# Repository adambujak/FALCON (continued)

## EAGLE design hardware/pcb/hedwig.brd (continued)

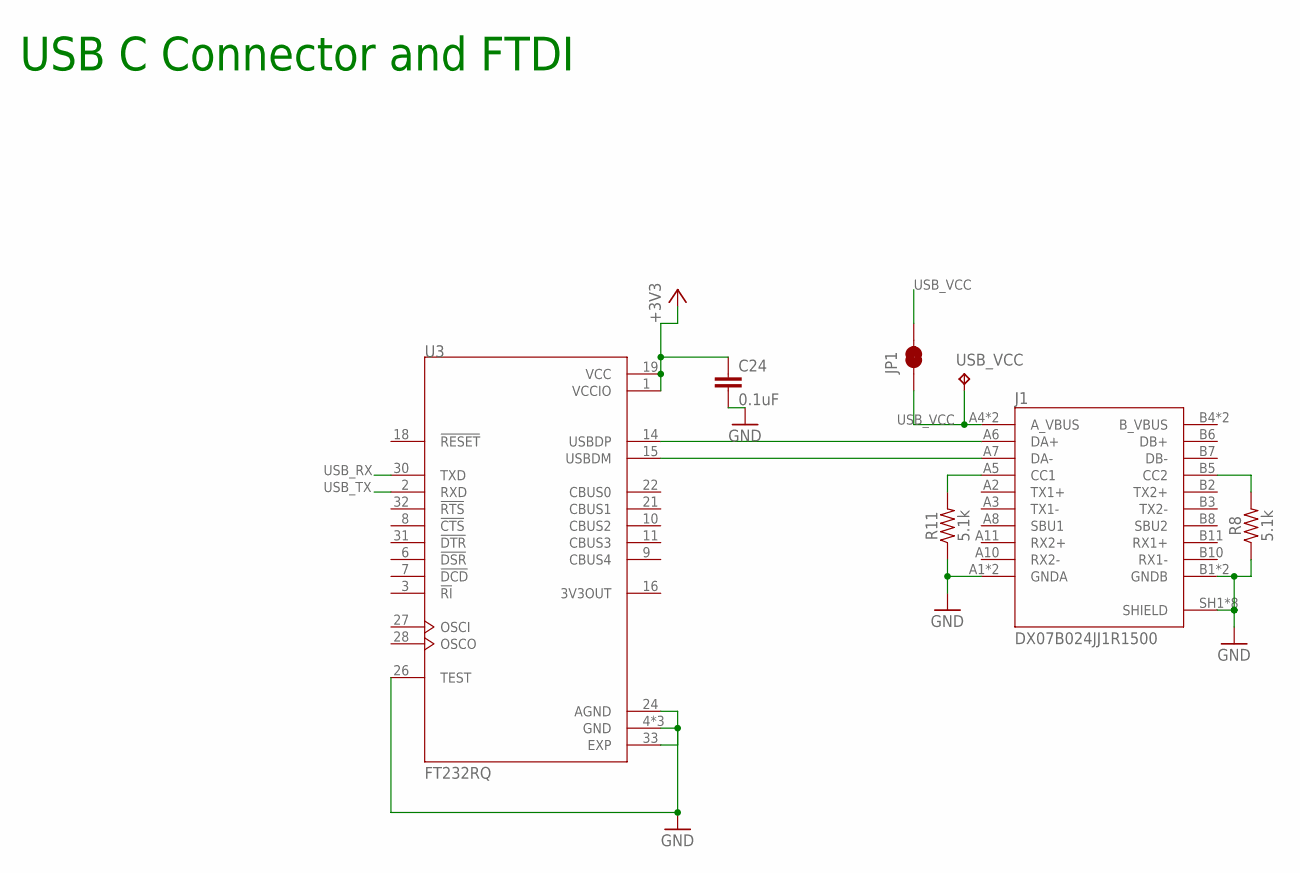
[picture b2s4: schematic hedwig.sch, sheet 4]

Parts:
C24: 0.1uF; 0603@1
J1: DX07B024JJ1R1500; JAE_DX07B024JJ1R1500
JP1: JUMPER-SMT_2_NC_TRACE_SILK; SMT-JUMPER_2_NC_TRACE_SILK
R8, R11: 5.1k; 0603
U3: FT232RQ; QFN50P500X500X90-33N
USB_VCC: TPB2,54; B2,54

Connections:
+3V3: C24.1, U3.1 (VCCIO), U3.19 (VCC); also elsewhere on the board
B_VBUS: J1.B4 (B_VBUS), J1.B9 (B_VBUS)
GND: C24.2, J1.A1 (GNDA), J1.A12 (GNDA), J1.B1 (GNDB), J1.B12 (GNDB), J1.SH1 (SHIELD), J1.SH2 (SHIELD), J1.SH3 (SHIELD), J1.SH4 (SHIELD), J1.SH5 (SHIELD), J1.SH6 (SHIELD), J1.SH7 (SHIELD), J1.SH8 (SHIELD), R8.1, R11.1, U3.4 (GND), U3.17 (GND), U3.20 (GND), U3.24 (AGND), U3.26 (TEST), U3.33 (EXP); also elsewhere on the board
unnamed: J1.B5 (CC2), R8.2
unnamed: J1.A6 (DA+), U3.14 (USBDP)
unnamed: J1.A7 (DA-), U3.15 (USBDM)
unnamed: J1.A5 (CC1), R11.2
USB_RX: U3.30 (TXD); also elsewhere on the board
USB_TX: U3.2 (RXD); also elsewhere on the board
USB_VCC: J1.A4 (A_VBUS), J1.A9 (A_VBUS), JP1.1, JP1.2, USB_VCC.TP; also elsewhere on the board

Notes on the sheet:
USB C Connector and FTDI

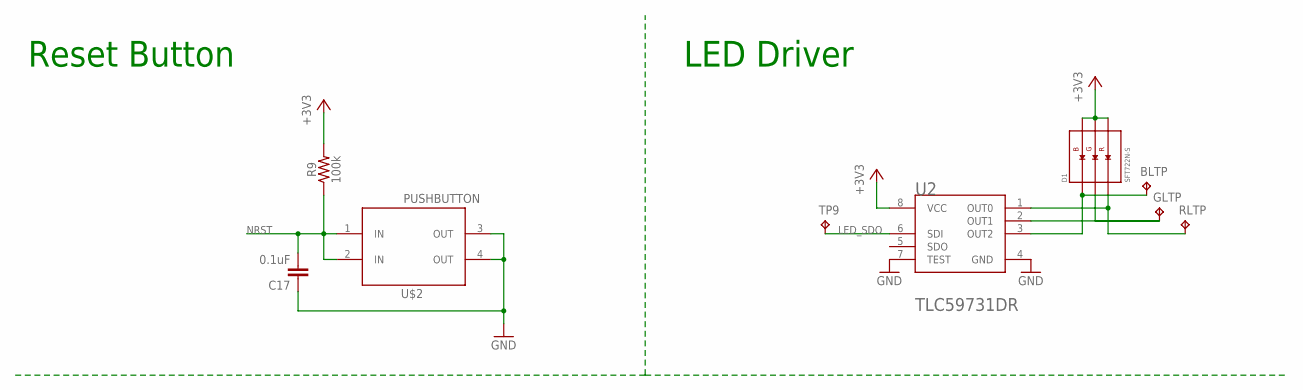
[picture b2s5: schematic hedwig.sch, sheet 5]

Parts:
BLTP: TPB1,27; B1,27
C17: 0.1uF; 0603
D1: SFT722N-S; LED_SFT722N-S
GLTP: TPB1,27; B1,27
R9: 100k; 0603
RLTP: TPB1,27; B1,27
TP9: TPB1,27; B1,27
U2: TEXAS_INSTRUMENTS_TLC59731DRTEXAS_INSTRUMENTS_TLC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; TEXAS_INSTRUMENTS_TLC59731DR_0
U$2: PUSHBUTTON; PUSH_BUTTON

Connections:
+3V3: D1.4 (RA), D1.5 (GA), D1.6 (BA), R9.2, U2.8 (VCC); also elsewhere on the board
GND: C17.1, U2.4 (GND), U2.7 (TEST), U$2.3 (OUT), U$2.4 (OUT); also elsewhere on the board
LED_SDO: TP9.TP, U2.6 (SDI); also elsewhere on the board
unnamed: BLTP.TP, D1.1 (BC), U2.3 (OUT2)
unnamed: D1.3 (RC), RLTP.TP, U2.1 (OUT0)
unnamed: D1.2 (GC), GLTP.TP, U2.2 (OUT1)
NRST: C17.2, R9.1, U$2.1 (IN), U$2.2 (IN); also elsewhere on the board

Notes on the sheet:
Reset Button
LED Driver

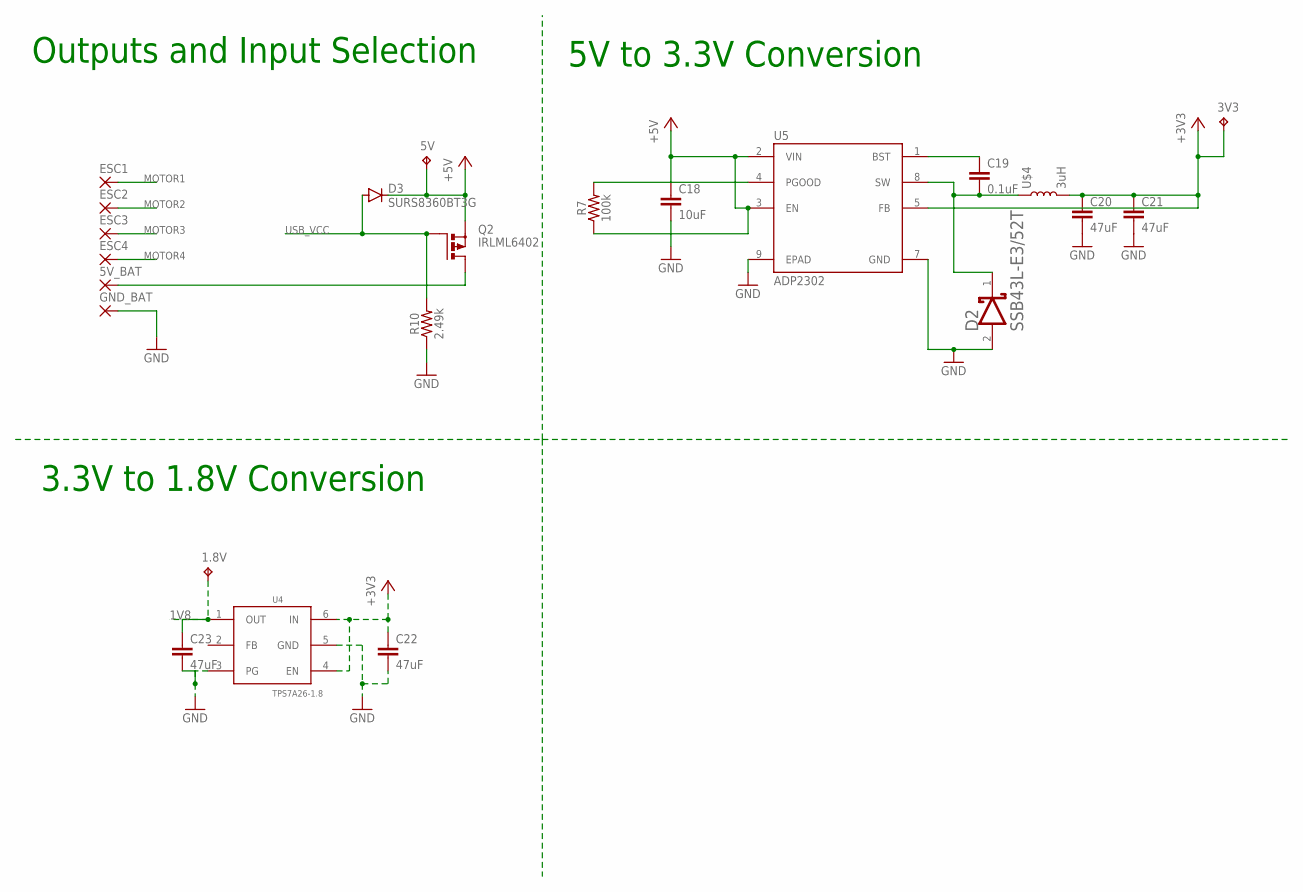
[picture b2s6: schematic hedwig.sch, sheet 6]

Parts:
1.8V, 3V3, 5V: TPB2,54; B2,54
5V_BAT: 2,54/1,0
C18: 10uF; 0603@1
C19: 0.1uF; 0603@1
C20, C21, C22, C23: 47uF; 0603@1
D2: SSB43L; VISHAY_SSB43L-E3-52T_0
D3: SURS8360BT3G; SMB
ESC1, ESC2, ESC3, ESC4: SMD2; SMD1,27-2,54
GND_BAT: 2,54/1,0
Q2: IRLML6402; SOT-23
R7: 100k; 0603
R10: 2.49k; 0603
U4: TPS7A26-1.8; WSON
U5: ADP2302; SOIC127P600X175-9N
U$4: 3uH; REG_INDUCTOR

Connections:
1V8: 1.8V.TP, C23.1, U4.1 (OUT); also elsewhere on the board
+3V3: 3V3.TP, C20.1, C21.1, C22.1, U4.4 (EN), U4.6 (IN), U5.5 (FB), U$4.@2 (2); also elsewhere on the board
+5V: 5V.TP, C18.1, D3.@2 (C), Q2.P2 (S), R7.1, U5.2 (VIN), U5.3 (EN)
GND: C18.2, C20.2, C21.2, C22.2, C23.2, D2.2 (ANODE), GND_BAT.1, R10.1, U4.3 (PG), U4.5 (GND), U5.7 (GND), U5.9 (EPAD); also elsewhere on the board
MOTOR1: ESC1.1; also elsewhere on the board
MOTOR2: ESC2.1; also elsewhere on the board
MOTOR3: ESC3.1; also elsewhere on the board
MOTOR4: ESC4.1; also elsewhere on the board
unnamed: C19.1, U5.1 (BST)
unnamed: R7.2, U5.4 (PGOOD)
unnamed: C19.2, D2.1 (CATHODE), U5.8 (SW), U$4.@1 (1)
unnamed: 5V_BAT.1, Q2.P3 (D)
USB_VCC: D3.@1 (A), Q2.P1 (G), R10.2; also elsewhere on the board

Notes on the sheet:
Outputs and Input Selection
5V to 3.3V Conversion
3.3V to 1.8V Conversion

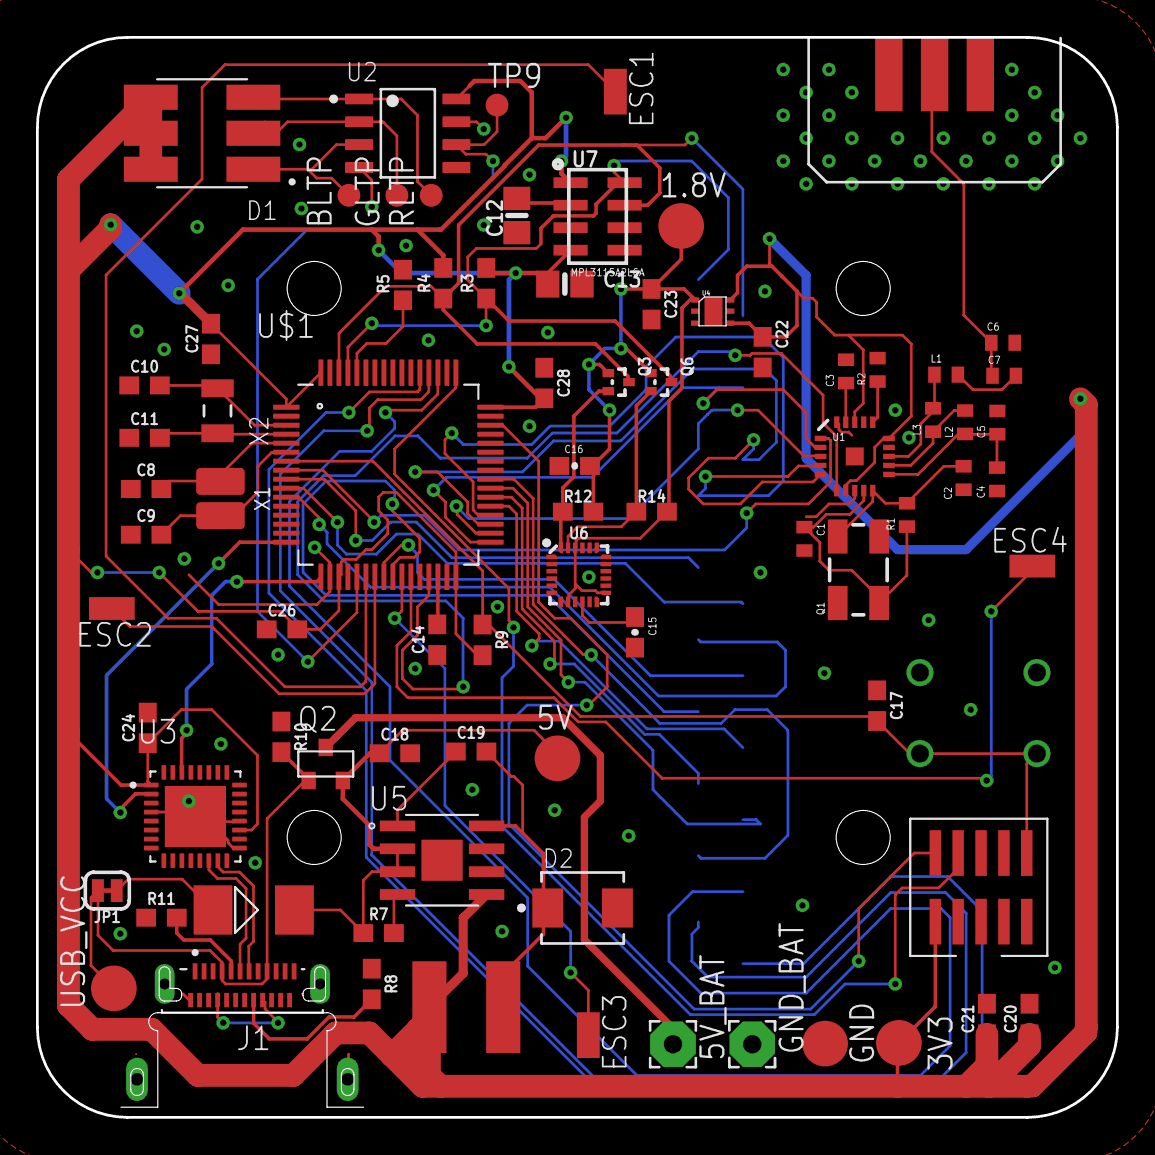
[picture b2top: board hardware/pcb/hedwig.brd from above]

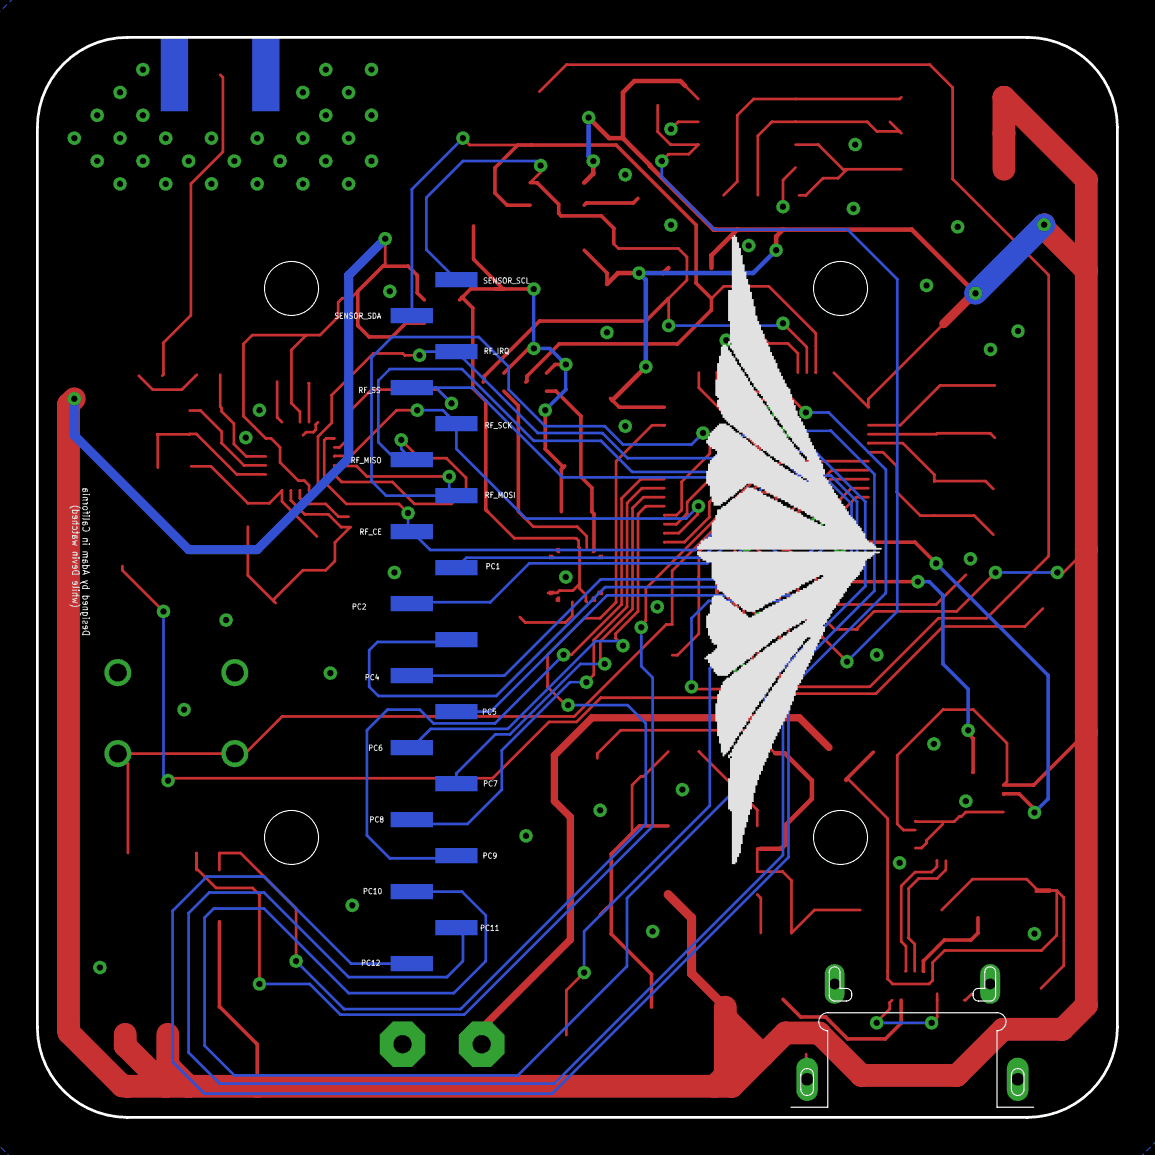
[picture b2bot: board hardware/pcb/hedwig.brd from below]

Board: 2 copper layers, 60.0 x 60.0 mm, 85 parts (5 on the bottom side), 66 nets.

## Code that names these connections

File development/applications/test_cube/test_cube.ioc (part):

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PB13.GPIOParameters=GPIO_Label
Mcu.UserName=STM32F412ZGTx
PD9.GPIOParameters=GPIO_Label
PA14.GPIO_Label=TCK
RCC.SYSCLKSourceVirtual=RCC_SYSCLKSOURCE_PLLCLK
PC6.GPIO_Label=RF_CE
PA3.GPIOParameters=GPIO_ModeDefaultPP
PB13.GPIO_Label=RF_SCK
PB13.Signal=SPI2_SCK
PB15.Signal=SPI2_MOSI
PD9.Mode=Asynchronous
RCC.SYSCLKSource=RCC_SYSCLKSOURCE_PLLCLK
PA3.GPIO_ModeDefaultPP=GPIO_MODE_AF_OD
PH0\ -\ OSC_IN.Signal=RCC_OSC_IN
PD8.GPIOParameters=GPIO_Label
PD8.Signal=USART3_TX
RCC.HSE_VALUE=8000000
PB12.GPIO_Label=RF_SS
PC14-OSC32_IN.Mode=LSE-External-Oscillator
PA14.Mode=Serial_Wire
PB14.Mode=Full_Duplex_Master
PB3.GPIOParameters=GPIO_Label
PH0\ -\ OSC_IN.GPIOParameters=GPIO_Label
PA13.GPIOParameters=GPIO_Label
Mcu.Package=LQFP144
PC6.GPIO_PuPd=GPIO_PULLUP
PB13.Mode=Full_Duplex_Master
PC6.GPIO_Speed=GPIO_SPEED_FREQ_HIGH
PA3.Signal=USART2_RX
PB3.GPIO_Label=SWO
PC15-OSC32_OUT.Mode=LSE-External-Oscillator
PD9.GPIO_Label=STLK_TX [STM32F103CBT6_PA2]
PH1\ -\ OSC_OUT.Mode=HSE-External-Clock-Source
PC6.Signal=GPIO_Output
PD9.Signal=USART3_RX
PC14-OSC32_IN.Signal=RCC_OSC32_IN
boardIOC=true
PD8.GPIO_Label=STLK_RX [STM32F103CBT6_PA3]
PA3.Mode=Asynchronous
PA13.Signal=SYS_JTMS-SWDIO
PH0\ -\ OSC_IN.Mode=HSE-External-Clock-Source
PC15-OSC32_OUT.Signal=RCC_OSC32_OUT
PD8.Mode=Asynchronous
PB10.Signal=GPXTI10
PB14.Signal=SPI2_MISO
PH1\ -\ OSC_OUT.Signal=RCC_OSC_OUT
board=NUCLEO-F412ZG
PB15.Mode=Full_Duplex_Master
PA13.Mode=Serial_Wire
Mcu.Name=STM32F412Z(E-G)Tx
PA2.Signal=USART2_TX
PA13.GPIO_Label=TMS
PB3.Signal=SYS_JTDO-SWO
RCC.SYSCLKFreq_VALUE=96000000
PA14.GPIOParameters=GPIO_Label
PA14.Signal=SYS_JTCK-SWCLK
PC6.GPIOParameters=GPIO_Speed,GPIO_PuPd,GPIO_Label
PA2.Mode=Asynchronous
PH0\ -\ OSC_IN.GPIO_Label=MCO
PB12.GPIOParameters=GPIO_Label
PB12.Signal=SPI2_NSS

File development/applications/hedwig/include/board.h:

#ifndef BOARD_H
#define BOARD_H

#include "stm32f4xx_hal.h"
#include "stm32f4xx_ll_bus.h"
#include "stm32f4xx_ll_gpio.h"
#include "stm32f4xx_ll_pwr.h"
#include "stm32f4xx_ll_rcc.h"
#include "stm32f4xx_ll_system.h"
#include "stm32f4xx_ll_tim.h"
#include "stm32f4xx_ll_usart.h"
#include "stm32f4xx_ll_utils.h"

#define SYSCLK_FREQ             96000000

/* System Time */
#define SYSTEM_TIME_TIMER       TIM2
#define SYSTEM_TIME_CLK_EN()    LL_APB1_GRP1_EnableClock(LL_APB1_GRP1_PERIPH_TIM2)

/* LEDS */
#ifdef BOARD_V1
#define FLN_LED_CLK_ENABLE()                     __HAL_RCC_GPIOA_CLK_ENABLE();
#define FLN_LED_PIN                              GPIO_PIN_5
#define FLN_LED_PORT                             GPIOA
#endif

#define FLN_LED_AF                               GPIO_AF2_TIM2
#define FLN_LED_TIMER                            TIM2
#define FLN_LED_TIMER_IRQ                        TIM2_IRQn
#define FLN_LED_TIMER_IRQ_Handler                TIM2_IRQHandler
#define FLN_LED_TIMER_CLK_ENABLE()               __HAL_RCC_TIM2_CLK_ENABLE()

/* UART */
#define UART                                     USART2
#define UART_CLK_EN()                            LL_APB1_GRP1_EnableClock(LL_APB1_GRP1_PERIPH_USART2)
#define GPIO_UART_CLK_EN()                       LL_AHB1_GRP1_EnableClock(LL_AHB1_GRP1_PERIPH_GPIOA)

#define UART_FORCE_RESET()                       __HAL_RCC_USART2_FORCE_RESET()
#define UART_RELEASE_RESET()                     __HAL_RCC_USART2_RELEASE_RESET()

#define UART_GPIO_PORT                           GPIOA
#define UART_GPIO_AF                             GPIO_AF7_USART2
#define UART_TX_PIN                              GPIO_PIN_2
#define UART_RX_PIN                              GPIO_PIN_3

#define UART_BAUDRATE                            1000000

#define UART_IRQn                                USART2_IRQn
#define UART_IRQHandler                          USART2_IRQHandler

/* Sensors */
#define FLN_SENSORS_I2C                          I2C1
#define FLN_SENSORS_I2C_CLK_ENABLE()             __HAL_RCC_I2C1_CLK_ENABLE()
#define FLN_SENSORS_I2C_SDA_GPIO_CLK_ENABLE()    __HAL_RCC_GPIOB_CLK_ENABLE()
#define FLN_SENSORS_I2C_SCL_GPIO_CLK_ENABLE()    __HAL_RCC_GPIOB_CLK_ENABLE()

#define FLN_SENSORS_I2C_FORCE_RESET()            __HAL_RCC_I2C1_FORCE_RESET()
#define FLN_SENSORS_I2C_RELEASE_RESET()          __HAL_RCC_I2C1_RELEASE_RESET()

#define FLN_SENSORS_I2C_SCL_PIN                  GPIO_PIN_8
#define FLN_SENSORS_I2C_SCL_GPIO_PORT            GPIOB
#define FLN_SENSORS_I2C_SDA_PIN                  GPIO_PIN_9
#define FLN_SENSORS_I2C_SDA_GPIO_PORT            GPIOB
#define FLN_SENSORS_I2C_SCL_SDA_AF               GPIO_AF4_I2C1

#define FLN_SENSORS_I2C_SPEEDCLOCK               400000
#define FLN_SENSORS_I2C_DUTYCYCLE                I2C_DUTYCYCLE_2

/* IMU */
#define IMU_IRQ_GPIO_CLK_ENABLE()                __HAL_RCC_GPIOA_CLK_ENABLE()
#define IMU_IRQ_PIN                              GPIO_PIN_8
#define IMU_IRQ_GPIO_PORT                        GPIOA

/* MOTORS */
#define FLN_MOTOR_TIMER                          TIM3
#define FLN_MOTOR_TIMER_CLK_ENABLE()             __HAL_RCC_TIM3_CLK_ENABLE()
#define FLN_MOTOR_GPIO_CLK_ENABLE()              __HAL_RCC_GPIOA_CLK_ENABLE(); \
  __HAL_RCC_GPIOB_CLK_ENABLE();

#define FLN_MOTOR_GPIO_PORT_CHANNEL1             GPIOA
#define FLN_MOTOR_GPIO_PORT_CHANNEL2             GPIOA
#define FLN_MOTOR_GPIO_PORT_CHANNEL3             GPIOB
#define FLN_MOTOR_GPIO_PORT_CHANNEL4             GPIOB
#define FLN_MOTOR_GPIO_PIN_CHANNEL1              GPIO_PIN_6
#define FLN_MOTOR_GPIO_PIN_CHANNEL2              GPIO_PIN_7
#define FLN_MOTOR_GPIO_PIN_CHANNEL3              GPIO_PIN_0
#define FLN_MOTOR_GPIO_PIN_CHANNEL4              GPIO_PIN_1
#define FLN_MOTOR_GPIO_AF_CHANNEL1               GPIO_AF2_TIM3
#define FLN_MOTOR_GPIO_AF_CHANNEL2               GPIO_AF2_TIM3
#define FLN_MOTOR_GPIO_AF_CHANNEL3               GPIO_AF2_TIM3
#define FLN_MOTOR_GPIO_AF_CHANNEL4               GPIO_AF2_TIM3

/* RF */
#define RF_SPI                                   SPI2
#define RF_SPI_CLK_ENABLE()                      __HAL_RCC_SPI2_CLK_ENABLE()
#define RF_SPI_SCK_GPIO_CLK_ENABLE()             __HAL_RCC_GPIOB_CLK_ENABLE()
#define RF_SPI_MISO_GPIO_CLK_ENABLE()            __HAL_RCC_GPIOB_CLK_ENABLE()
#define RF_SPI_MOSI_GPIO_CLK_ENABLE()            __HAL_RCC_GPIOB_CLK_ENABLE()
#define RF_GPIO_CLK_ENABLE()                     __HAL_RCC_GPIOB_CLK_ENABLE(); \
  __HAL_RCC_GPIOC_CLK_ENABLE()
#define RF_IRQ_GPIO_CLK_ENABLE()                 __HAL_RCC_GPIOB_CLK_ENABLE()

#define RF_SPI_FORCE_RESET()                     __HAL_RCC_SPI2_FORCE_RESET()
#define RF_SPI_RELEASE_RESET()                   __HAL_RCC_SPI2_RELEASE_RESET()

#define RF_IRQ_PIN                               GPIO_PIN_10
#define RF_IRQ_GPIO_PORT                         GPIOB
#define RF_CE_PIN                                GPIO_PIN_6
#define RF_CE_GPIO_PORT                          GPIOC
#define RF_SPI_SS_PIN                            GPIO_PIN_12
#define RF_SPI_SS_GPIO_PORT                      GPIOB
#define RF_SPI_SCK_PIN                           GPIO_PIN_13
#define RF_SPI_SCK_GPIO_PORT                     GPIOB
#define RF_SPI_SCK_AF                            GPIO_AF5_SPI2
#define RF_SPI_MISO_PIN                          GPIO_PIN_14
#define RF_SPI_MISO_GPIO_PORT                    GPIOB
#define RF_SPI_MISO_AF                           GPIO_AF5_SPI2
#define RF_SPI_MOSI_PIN                          GPIO_PIN_15
#define RF_SPI_MOSI_GPIO_PORT                    GPIOB
#define RF_SPI_MOSI_AF                           GPIO_AF5_SPI2

#endif  // BOARD_H

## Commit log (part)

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2020-10-05 Format code
2020-10-05 Move bringup code to bsp
2020-10-06 Add tags to gitignore
2020-10-06 gitignore update and cleanup (#12)
    * Remove unused function prototype
    * Add tags to gitignore
2020-10-15 i2c working
2020-10-16 added mpu sdk
2020-10-16 Simplify logger and implement macro
2020-10-16 review changes
2020-10-17 changed to HAL_mem_read/write, works on both sensors now
2020-10-17 add std gnu flag (#17)
2020-10-17 Rename i2c module definitions
2020-10-17 Add -Werror flag to makefile
2020-10-17 Add sensors i2c
2020-10-17 Fix function declarations to match functions defs
2020-10-17 Change pins
2020-10-21 Add motor control with PWM (#18)
    * Add motor control with PWM
    * Change pins
    * Fix assert
2020-10-21 Add custom spi functions to HAL
2020-10-25 Add pcb and schematic
2020-10-26 updated schematic and pcb
2020-10-27 add flash python script and add to makefile
2020-10-28 Pcb overhall - put imu in middle, made board square
2020-10-28 Add logo to that pcb
2020-10-28 Added pics, pdf, fixed silkscreen, and added more vias
2020-10-29 working with restart
2020-10-30 sending frf
2020-10-31 getting interrupt from rx
2020-10-31 fix max_rt bug
2020-10-31 Move rx clear rxPowerUp
2020-11-04 grabbed modified mpu9250 python stuff
2020-11-06 Fix major issues in hardware
2020-11-09 added ICM and fimu stuff to makefile
2020-11-10 added driver dependency files
2020-11-10 added working fimu library files
2020-11-11 add flash python script and add to makefile (#20)
2020-11-11 - Add support for new board - Fix FreeRTOS delay bug (if delayed before scheduler starts, hard fault) - Code cleanup in bsp
2020-11-11 add jlink serial id
2020-11-11 Add support for new board and some other fixes (#23)
    * - Add support for new board
    - Fix FreeRTOS delay bug (if delayed before scheduler starts, hard fault)
    - Code cleanup in bsp
    * add jlink serial id
2020-11-12 working
2020-11-12 added set color function to header
2020-11-12 Abstract timer handler
2020-11-13 rf working
2020-11-13 Fix FRF library, and add to stm (#26)
    * - Add support for new board
    - Fix FreeRTOS delay bug (if delayed before scheduler starts, hard fault)
    - Code cleanup in bsp
    * Add custom spi functions to HAL
    Add spi to v2 app and add frf
    Sending data
2020-11-13 Add support for LED driver on new board (#25)
    * LED ON
    * working
    * Blinking led
    * added set color function to header
    * Abstract timer handler
2020-11-15 removed WError for now
2020-11-15 added MPL driver
2020-11-15 general setup for sensors task
2020-11-15 updated sensors task for different rate barometer readings
2020-11-15 sensors task and barometer library setup
2020-11-15 improved fbaro calibration function
2020-11-19 added motor init function from testing on hardware
2020-12-17 changes for new board
2020-12-17 add ozone debug files
2020-12-17 schematic and pcb update
2020-12-22 Reduce motor delay time, and increase sensor task priority
2020-12-30 fix irq naming for imu
2021-01-29 add albus - stm32
    deleted eclipse
    Add frf process so it'll work
2021-01-29 fix disco board issue in makefile
2021-01-29 implement radio common into device com
2021-01-30 RF packets sending back and forth feature (#28)
    * add assert to both hedwig and albus
    * add albus - stm32
    deleted eclipse
    Add frf process so it'll work
    * add radio common to makefile
    * fix disco board issue in makefile
2021-02-01 Schematic Update - Fix USB C port reversablilty issue Board Update - Fix USB C port reversablilty issue BOM Update - Fix incorrect logic level shift FET - Fix multiple entries for same parts
2021-03-13 add grinbuf
2021-03-13 Merge grinbuf library and test infrastructure (#30)
    * add grinbuf
    * add testing framework
2021-03-13 add falcon packet lib
2021-03-13 change VDISCO to DISCO
2021-03-14 increase stack and heap size for albus
2021-03-14 Add common defines
2021-03-14 changes to frf
2021-03-14 albus device com changes
2021-03-14 Sending falcon packets back and forth (#33)
    * changes to frf
    * albus device com changes
    * hedwig changes to receive falcon packets
2021-03-14 fix makefile board define
2021-03-14 fix makefile includes
2021-03-14 rename falcon_v2 to hedwig
2021-03-14 rename falcon_v2 to hedwig (#35)
2021-03-14 fix test paths (#37)
2021-03-14 sensors task running alongside device com
2021-03-14 temp sensors.c commit
2021-03-14 renamed modes
2021-03-14 fix for imu hook file using taskDelay
2021-03-15 clean up makefile output
2021-03-15 remove eclipse files"
2021-03-15 add python packet generation
2021-04-02 add power of two assert
2021-04-02 receiving packets - todo figure out python exit
2021-04-02 was working before but not receiving uart now
2021-04-02 start adding cornelius
2021-04-02 monitor scrolling
2021-04-02 new albus has uart
2021-04-02 albus rewrite
2021-04-02 cornelius serial monitor scrolling back to top
2021-04-02 sending frames to albus
2021-04-02 fix system time hard fault
2021-04-02 cleanup main
2021-04-02 add led toggle to error handler and start device com task
2021-04-02 wrap up system time
2021-04-02 I went beast mode by accident - Implement new logger interface - Start deleting bsp from hedwig - Fix clock issue on hedwig - Fix makefile hedwig
2021-04-02 big rewrite (#40)
    * start adding cornelius
    * update python fp to return encoded bytearray
    * monitor scrolling
    * was working before but not receiving uart now
    * receiving packets - todo figure out python exit
    * idk
2021-04-03 gettign interrupts now
    revert ld
2021-04-03 revert hedwig changes'
2021-04-03 fix rf on albus (#41)
    fix rf on albus,
    add hal back
2021-04-03 change system time variable names (#42)
    move system time to common
    fix board.h
2021-04-05 remove fifo
2021-04-05 change delay from us
2021-04-05 sending ack with payload
2021-04-05 remove frf mutex
2021-04-05 move decoder into device com
2021-04-05 move sending and getting into device com
2021-04-05 add public radio functions
2021-04-05 add radio fifo
2021-04-05 decouple frf_getPacket
2021-04-05 lower device com priority
2021-04-05 Radios talking reliably back and forth with acks (#43)
    * speed up write time
    * working with dynamic
    * sending ack with payload
    * change delay from us
    * remove unnecessary irq clear
    * remove fifo
2021-04-09 fix warnings in ICM driver
2021-04-09 add ozone files to gitignore
2021-04-09 change clang-format
2021-04-09 change log levels
2021-04-09 general cleanup
2021-04-09 radio naming and logic changes
2021-04-09 change radio functions
2021-04-09 change system time timer
2021-04-10 run formatter
2021-04-10 formatter changes
2021-04-10 add artwork
2021-04-11 data from device com into flight control using mutex
2021-04-11 tried to implement task notif for flight control
2021-04-11 got software timer working with task notification
2021-04-11 added function for getting output data from flight control
2021-04-11 added simple FC mode support to RF stuff, hedwig side sending stuff added but commentented out
2021-04-11 turned on sensors and FC in main, rename in FC xTaskCreate
2021-04-11 MAJOR ERROR LOCATED
2021-04-11 fixed barometer problem, device com sensors and FC working at once
2021-04-11 cleanup
2021-04-11 update clang_format switch case indent
2021-04-11 add fifo to makefile
2021-04-11 fix falcon packet bugs
2021-04-11 remove albus test code
2021-04-11 change falcon packet decoding scheme - include header all the way through
2021-04-11 device com sending nicely
2021-04-11 add features to falcon packet
2021-04-11 fixup hedwig device com
2021-04-11 renamed rf_process and added writing back to cornelius
2021-04-11 add packet queuing to hedwig
2021-04-12 created motors emergency stop and added to all error handlers
2021-04-12 changed to motors_off call in FC
2021-04-12 add sending test response to device com
2021-04-12 disable logging on albus
2021-04-12 Finally sending data through system (#50)
    * add new packet for testing
    ''
    * add sending test response to device com
    * disable logging on albus
    * disable gui, and send test query
2021-04-12 remove *.pyc files from repo
2021-04-12 add decode functions to falcon_packet
2021-04-12 fixed fp
2021-04-12 Add decode to python fp (#51)
    * remove *.pyc files from repo
    * add decode functions to falcon_packet
    * remove test function from cornelius
    * fixed fp
2021-04-14 make flashing more betterer for hedwig
2021-04-15 current debug session
2021-04-15 change time
2021-04-15 add decoder
2021-04-15 add to dict method
2021-04-15 add radio stats packet
2021-04-15 remove vscode files
2021-04-15 fix falcon packet path
2021-04-16 Sending data back and forth from cornelius (#54)
    * current debug session
    * change time
    * revert albus changes
    * add decoder
    * add to dict method
    * add input to cornelius.py
2021-04-16 add stm32cubide folder to gitignore
2021-04-17 update clang format
2021-04-17 add falcon_packet
2021-04-17 add c ringbuf and libcrc
2021-04-17 update libraries to use submodules properly (#56)
    * remove libcrc and c-ringbuf
    * delete falcon_packet
    * add falcon_packet
    * add c ringbuf and libcrc
    * update falcon packet
2021-04-17 fixed path in unity submodule (#57)
2021-04-17 update falcon_packet lib
2021-04-18 calibration command working
2021-04-18 remove unused led code
2021-04-18 modified calib enum
2021-04-20 Change device com - Always send multiple of 32 to radio - Add status process
2021-04-20 add radio status logging
2021-04-20 adam fix this loser
2021-04-20 increase data rate on radio
2021-04-20 lower rf_tx interval on albus
2021-04-20 changes to python
2021-04-20 increase radio tx buffer size
2021-04-23 setting up for rotor stand test
2021-04-27 minor fixes to sensor libs
2021-04-28 tunable parameter testing working
2021-05-07 kind of working
2021-05-07 added PID param tuning commands, falcon was hovering somewhat stably on test stand before disaster struck
2021-05-18 made hover constant a tunable parameter
2021-05-19 seperated controller params into seperate packets
2021-05-19 cornelius auto connects to albus
2021-06-03 gui done
2021-06-03 start gui
2021-06-03 fixed auto connecting
2021-06-03 made it nice with cornelius imported
2021-06-03 made the altitude submit button work properly
2021-07-17 gutted not working very well
2021-07-18 found issue
2021-07-21 added dt to madgwick library
2021-07-21 running fly mode with new attitude, pretty good. Needs some fine tuning and testing
2021-07-22 adam is a nitpicky lil bitch
2021-07-23 kind of working with both baro and imu
2021-07-23 un commented device com start
2021-07-26 added back and interfaced the old ICM driver with the new imu.c file format
2021-07-27 uart speed 1000000
2021-07-27 added compass
2021-08-13 added imu calibration
2021-08-23 add feature
2021-08-23 add led fix
2021-08-23 persistent data working with imu bias
2021-08-23 saving and loading controller params
2021-08-24 fix bug in yaw print statement
2022-06-06 idk what's on here
2022-11-22 Change default albus build to nucleo and change spi pins
2022-11-22 Add async logger and interrupt driven uart driver (#68)
    - Use LL for uart module
2022-11-22 Add async log fixes
2022-11-24 changed rf logs to DEBUG
2022-11-24 minor changes for flight testing
2022-11-24 Separate rtos tick calc
2022-11-25 Separate rtos tick calc (#72)
2022-11-25 Add uart input to hedwig (#73)
2022-11-25 add formatter
2022-11-25 Add code formatter and run it against codebase (#74)
    * add formatter
    * update blacklist
    * run formatter
2022-11-25 Fix assert_param warnings
2022-11-25 Fix compiler warnings
